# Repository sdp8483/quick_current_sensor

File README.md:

# Quick Current Sensor

This is a current sensor of various ranges for DC current measurements. The number one goal of this project was to make a set of current sensors only using what I have on hand, no buying anything. Also this has to be a simple design that gets the job done. It is not then best design and will not be the most accurate so it requires characterization before use. I suggest finding a better design with properly selected components, I suggest looking into the INA series of current sense amplifiers from TI that would make a better opamp to use then the old LM358. Again the only goal of this project is to use what I have already and not to waste time searching for the perfect components. Searching for the perfect components and design is what has stalled this project for years. That is just my way of defending the terrible design decisions made here and why you should look somewhere else for a current sensor.

### Calculations
[Google Sheets Link](https://docs.google.com/spreadsheets/d/1N8hUBOZxmFQPPFe9W_K_Z5sfmQMQ_LQjQ09W4D_ssm8/edit?usp=sharing)

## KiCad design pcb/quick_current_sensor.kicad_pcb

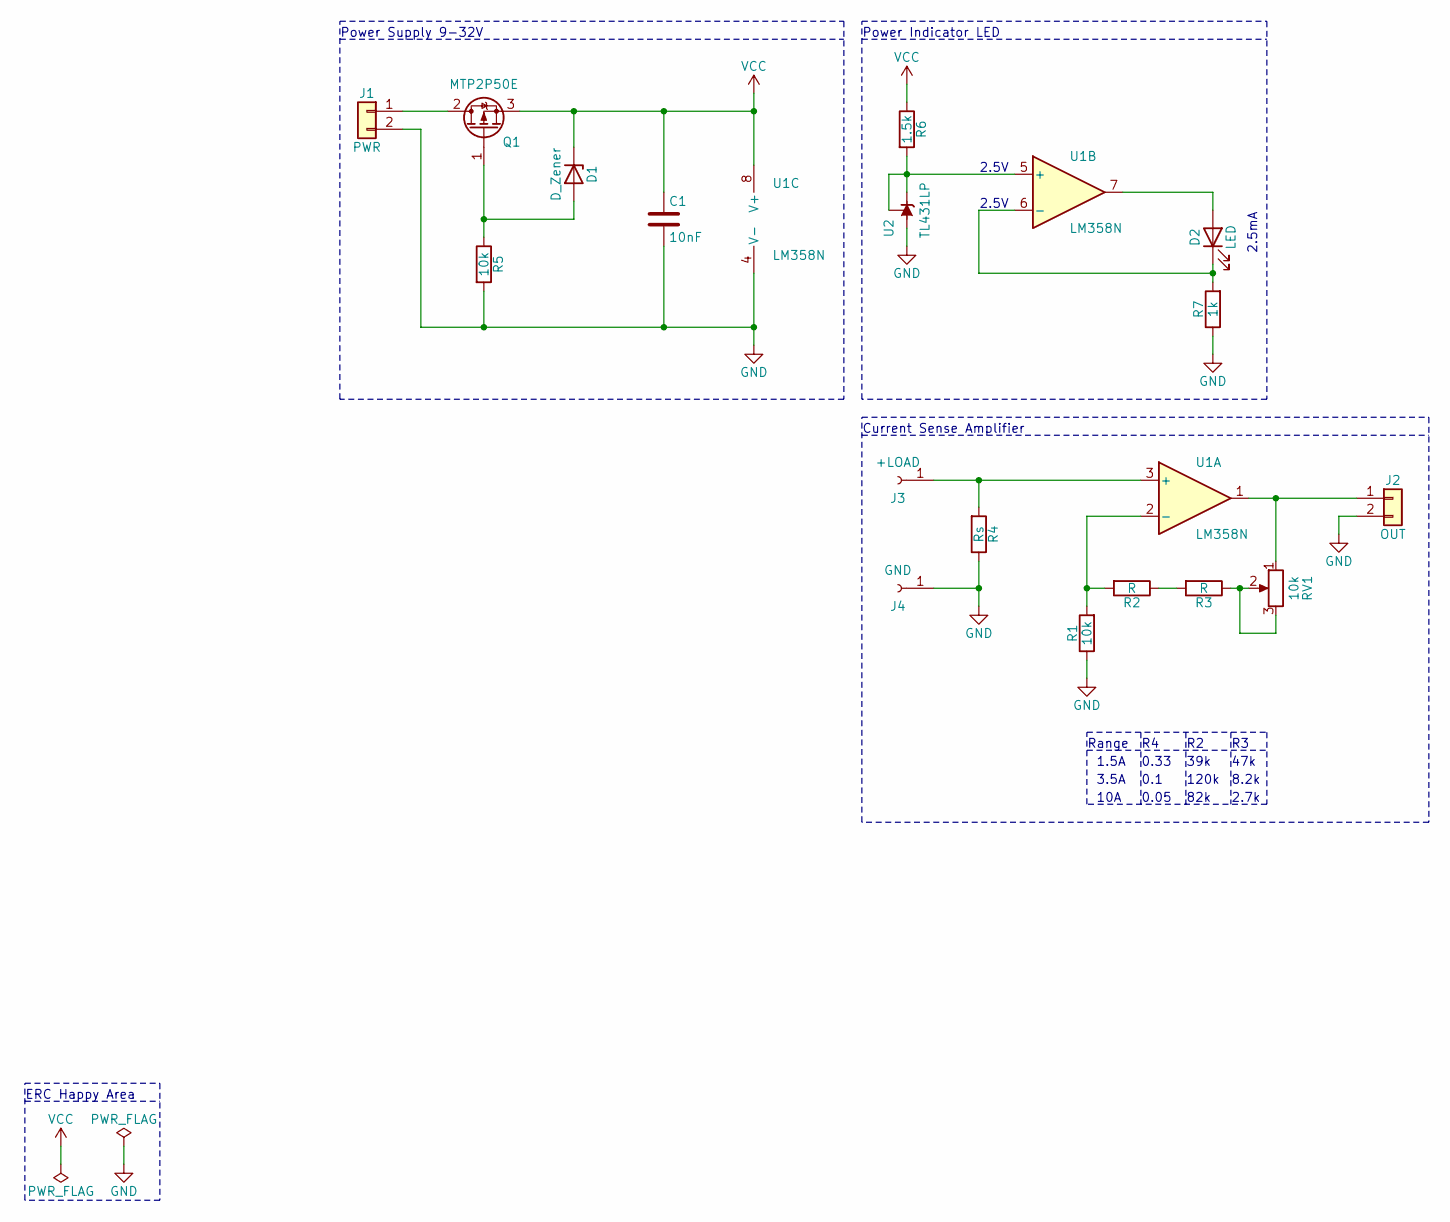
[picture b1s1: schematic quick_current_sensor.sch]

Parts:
C1: 10nF; C_0805_2012Metric_Pad1.18x1.45mm_HandSolder
D1: D_Zener; Nexperia_BZV55_SOD80C
D2: LED; LED_D3.0mm
J1: PWR; WJ127-5.0-2P
J2: OUT; WJ127-5.0-2P
J3: +LOAD; banana_edge_mount
J4: GND; banana_edge_mount
Q1: MTP2P50E; TO-220-3_Horizontal_TabUp
R1, R5: 10k; R_Axial_DIN0207_L6.3mm_D2.5mm_P10.16mm_Horizontal
R2, R3: R; R_Axial_DIN0207_L6.3mm_D2.5mm_P10.16mm_Horizontal
R4: Rs; RH-10
R6: 1.5k; R_Axial_DIN0207_L6.3mm_D2.5mm_P10.16mm_Horizontal
R7: 1k; R_Axial_DIN0207_L6.3mm_D2.5mm_P10.16mm_Horizontal
RV1: 10k; Potentiometer_Bourns_3006P_Horizontal
U1: LM358N; DIP-8_W7.62mm_LongPads
U2: TL431LP; TO-92_W4.0mm_StaggerEven_Horizontal_FlatSideDown

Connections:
GND: C1.2, J1.2, J2.2, J4.1, R1.1, R4.1, R5.2, R7.1, U1.4 (V-), U2.2 (A)
unnamed: D1.2 (A), Q1.1 (G), R5.1
unnamed: D2.1 (K), R7.2, U1.6 (-)
unnamed: D2.2 (A), U1.7
unnamed: J1.1, Q1.2 (D)
unnamed: J2.1, RV1.1, U1.1
unnamed: J3.1, R4.2, U1.3 (+)
unnamed: R1.2, R2.2, U1.2 (-)
unnamed: R2.1, R3.2
unnamed: R3.1, RV1.2, RV1.3
unnamed: R6.2, U1.5 (+), U2.1 (REF), U2.3 (K)
VCC: C1.1, D1.1 (K), Q1.3 (S), R6.1, U1.8 (V+)

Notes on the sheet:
Range
1.5A
3.5A
10A
0.33
0.1
0.05
39k
120k
82k
47k
8.2k
2.7k
2.5V
2.5mA
Power Supply 9-32V
Power Indicator LED
Current Sense Amplifier
ERC Happy Area

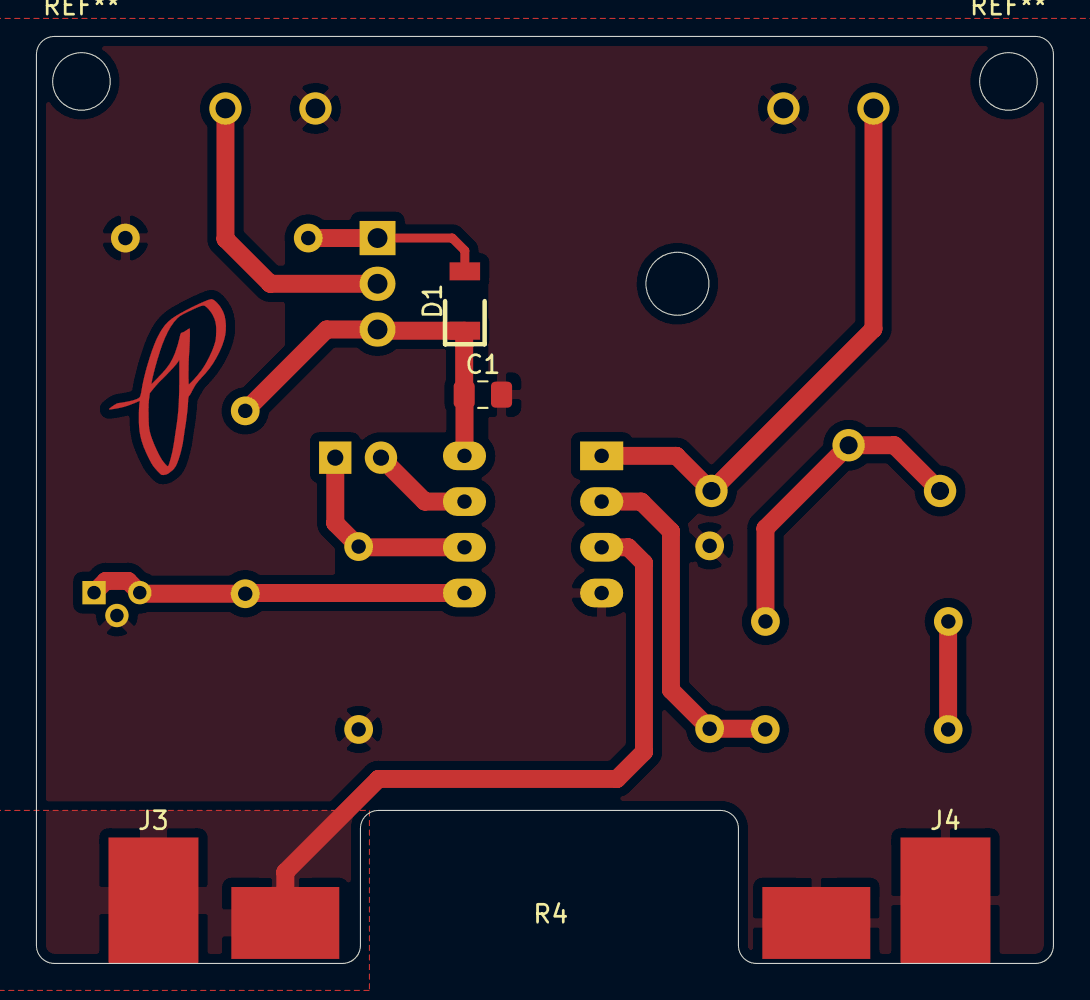
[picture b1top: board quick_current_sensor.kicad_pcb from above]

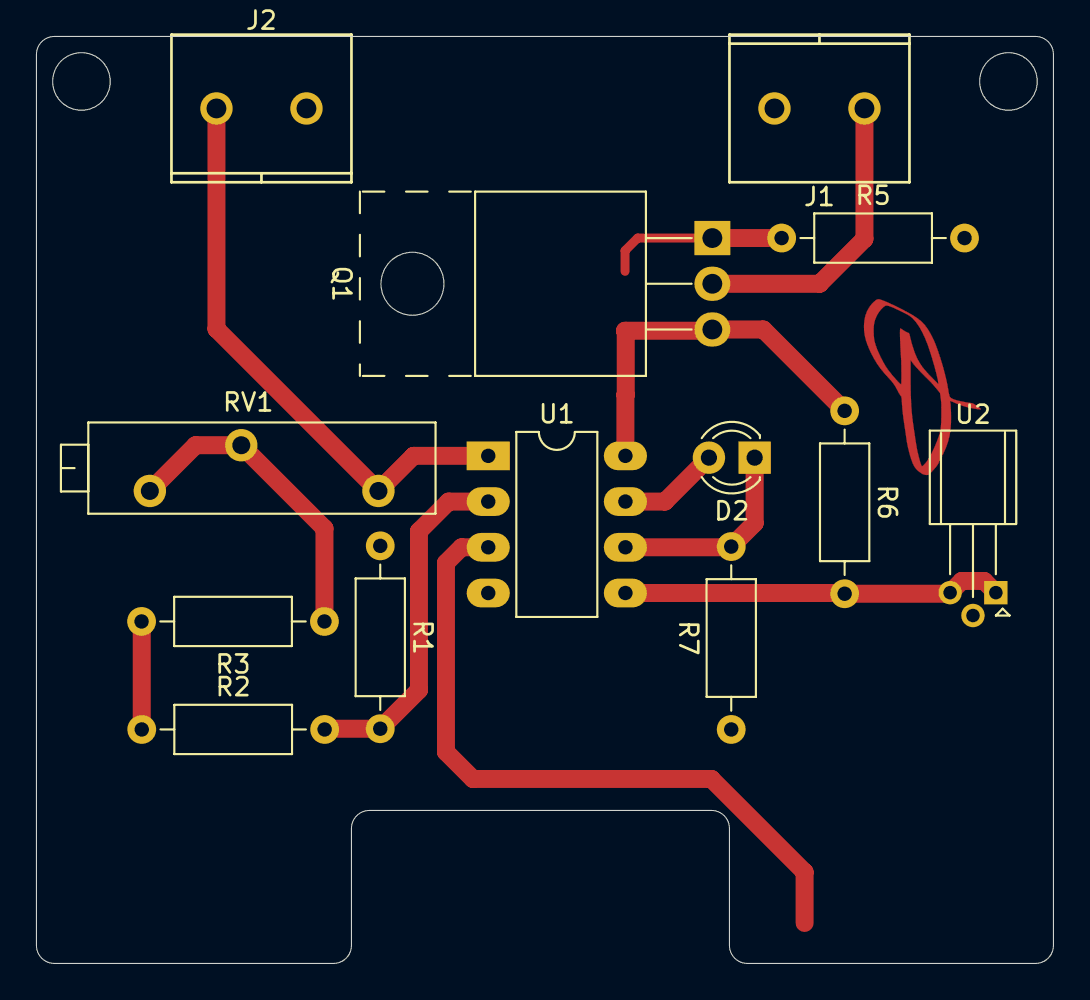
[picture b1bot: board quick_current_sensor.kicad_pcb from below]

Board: 2 copper layers, 56.5 x 51.5 mm, 18 parts (13 on the bottom side), 12 nets.

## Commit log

2021-01-10 init commit
2021-01-12 add Rs footprint and 3d model
2021-01-13 cleanup and add logo
2021-01-13 start enclosure design
2021-01-14 change power and vout to terminal blocks
2021-01-14 cleanup, reduce size
2021-01-15 updated enclosure for new IO
2021-01-15 added banana cutouts
2021-01-15 sink top screw heads
2021-01-15 add material around screw holes
2021-01-15 generate gerbers
2021-01-15 plot schematic pdf
2021-01-16 generate pcb gcode
2021-01-16 create ibom and pdf
2021-01-16 plot pdf
2021-01-16 mirror labeling to match PCB
2021-01-16 reduce edge chamfer
2021-01-16 change font
2021-01-16 increase pannel banana hole clearance
2021-01-17 export 3d files
2021-01-24 add jupyter notebooks used to characterize sensors
2021-01-24 brother PT-D600 24mm label
